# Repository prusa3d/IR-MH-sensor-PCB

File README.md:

# PRUSA IR-MH sensor board

KiCad PCB layout

* [Interactive bom](http://htmlpreview.github.io/?https://github.com/prusa3d/IR-MH-sensor-PCB/blob/master/rev.02/ibom.html)
* [STEP 3D model](rev.02/IR-MH-sensor-02.step)

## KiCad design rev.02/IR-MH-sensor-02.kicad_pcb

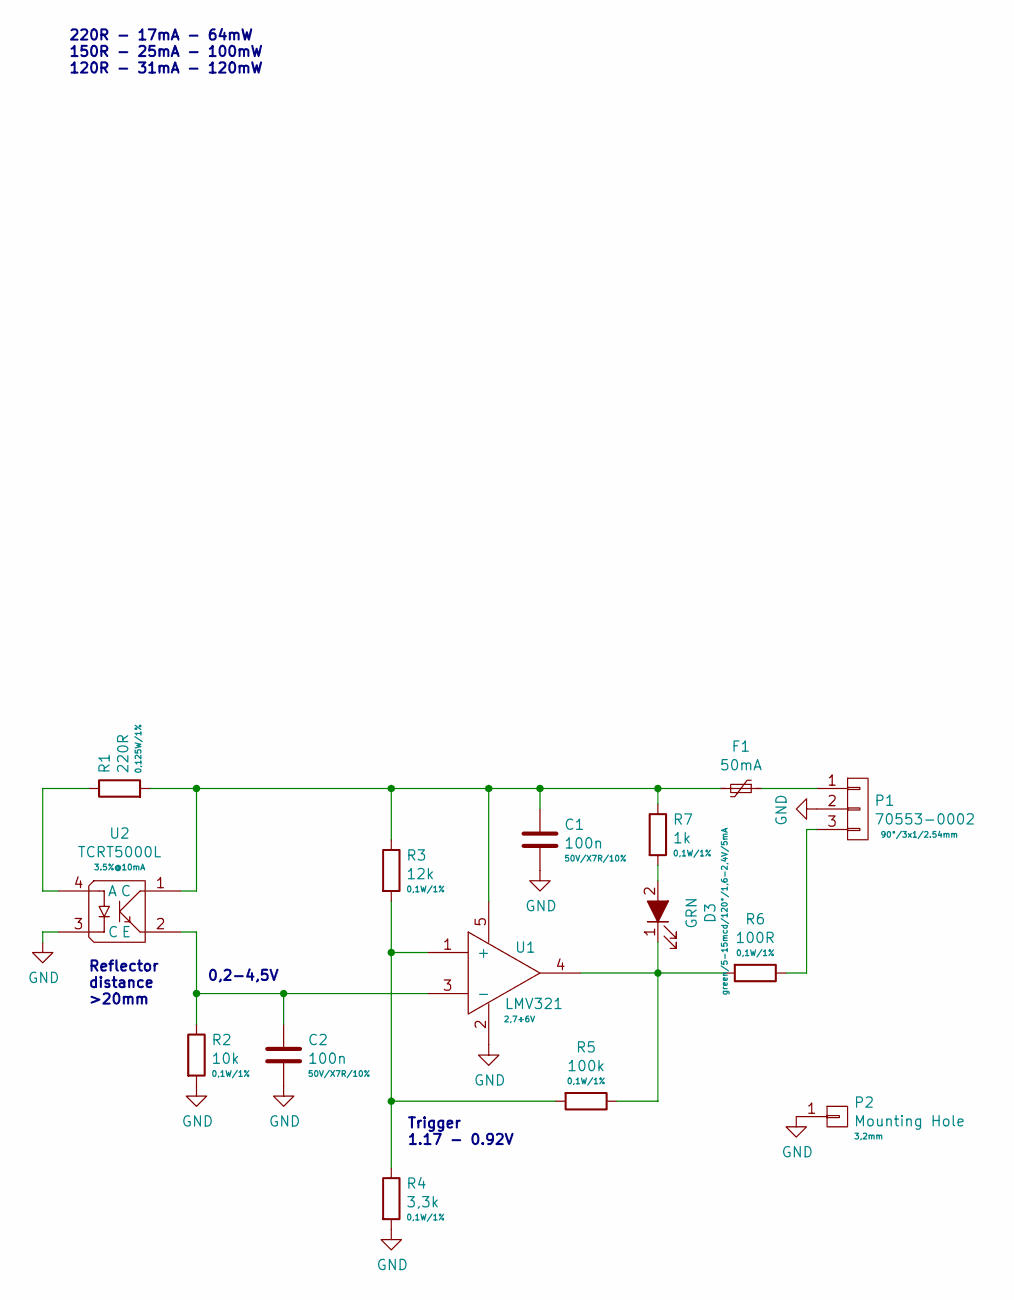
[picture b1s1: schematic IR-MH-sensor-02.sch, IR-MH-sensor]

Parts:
C1, C2: 100n; C_0603
D3: GRN; LED_0603
F1: 50mA; R_1206
P1: 70553-0002; Pin_Header_Angled_1x03
P2: Mounting Hole; MountingHole_3.2mm_M3_DIN965_Pad
R1: 220R; R_0805
R2: 10k; R_0603
R3: 12k; R_0603
R4: 3,3k; R_0603
R5: 100k; R_0603
R6: 100R; R_0603
R7: 1k; R_0603
U1: LMV321; SOT-23-5
U2: TCRT5000L; TCRT5000

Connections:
GND: C1.2, C2.2, P1.2, P2.1, R2.2, R4.2, U1.2, U2.3 (C)
unnamed: C1.1, F1.2, R1.2, R3.1, R7.1, U1.5, U2.1 (C)
unnamed: C2.1, R2.1, U1.3 (-), U2.2 (E)
unnamed: D3.1 (K), R5.1, R6.2, U1.4
unnamed: D3.2 (A), R7.2
unnamed: F1.1, P1.1
unnamed: P1.3, R6.1
unnamed: R1.1, U2.4 (A)
unnamed: R3.2, R4.1, R5.2, U1.1 (+)

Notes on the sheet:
Reflector distance >20mm
0,2-4,5V
Trigger 1.17 - 0.92V
220R - 17mA - 64mW 150R - 25mA - 100mW 120R - 31mA - 120mW

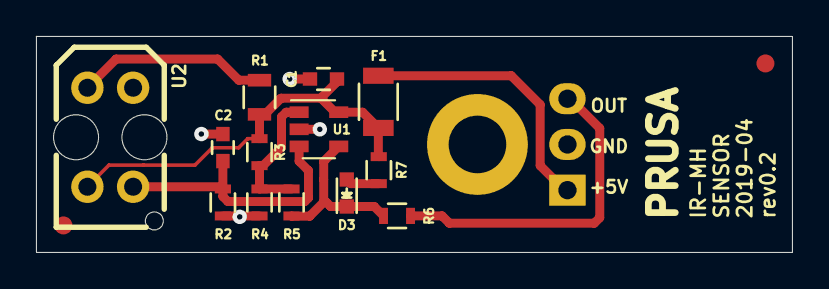
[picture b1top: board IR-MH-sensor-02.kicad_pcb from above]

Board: 2 copper layers, 42.0 x 12.0 mm, 15 parts (1 on the bottom side), 9 nets.

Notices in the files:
rev.02/IR-MH-sensor-02.sch:
http://creativecommons.org/licenses/by-sa/4.0
Licensed under the Attribution-ShareAlike 4.0 International (CC BY-SA 4.0)
